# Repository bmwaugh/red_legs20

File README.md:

# red_legs20
Git Repository for Red Legs 20 MQP

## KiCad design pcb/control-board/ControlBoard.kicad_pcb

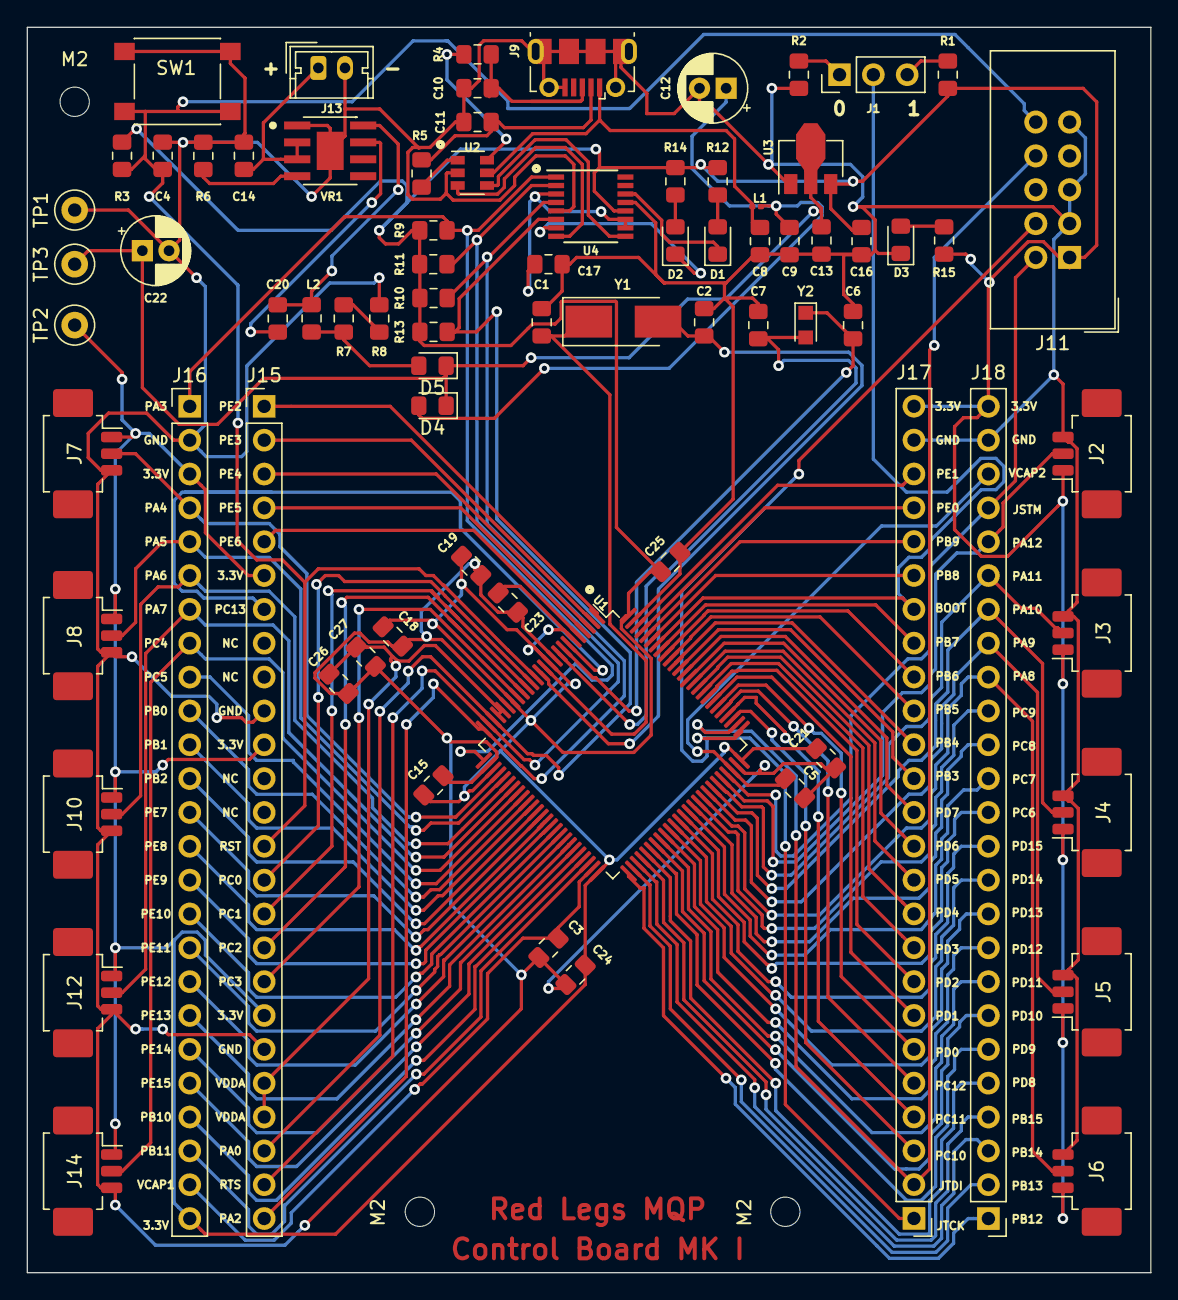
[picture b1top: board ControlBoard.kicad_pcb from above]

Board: 2 copper layers, 84.3 x 93.5 mm, 81 parts (0 on the bottom side), 112 nets.

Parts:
C1, C2: 22p; C_0805_2012Metric_Pad1.15x1.40mm_HandSolder
C3, C5, C14: 2.2uF; C_0805_2012Metric_Pad1.15x1.40mm_HandSolder
C4: 0.1uF; C_0805_2012Metric_Pad1.15x1.40mm_HandSolder
C6, C7: 10p; C_0805_2012Metric_Pad1.15x1.40mm_HandSolder
C8: 10nF; C_0805_2012Metric_Pad1.15x1.40mm_HandSolder
C9, C15, C17, C18, C19, C21, C23, C24, C25, C26: 100nF; C_0805_2012Metric_Pad1.15x1.40mm_HandSolder
C10, C11: 47pF; C_0805_2012Metric_Pad1.15x1.40mm_HandSolder
C12: 4.7uF; CP_Radial_D5.0mm_P2.00mm
C13, C16, C27: 1uF; C_0805_2012Metric_Pad1.15x1.40mm_HandSolder
C20: 2.2nF; C_0805_2012Metric_Pad1.15x1.40mm_HandSolder
C22: 47uF; CP_Radial_D5.0mm_P2.00mm
D1, D2, D3: LED; LED_0805_2012Metric_Pad1.15x1.40mm_HandSolder
D4, D5: SD0805; D_0805_2012Metric_Pad1.15x1.40mm_HandSolder
J1: BOOT0; PinHeader_1x03_P2.54mm_Vertical
J2: Motor1; Molex_PicoBlade_53261-0371_1x03-1MP_P1.25mm_Horizontal
J3: Motor2; Molex_PicoBlade_53261-0371_1x03-1MP_P1.25mm_Horizontal
J4: Motor3; Molex_PicoBlade_53261-0371_1x03-1MP_P1.25mm_Horizontal
J5: Motor4; Molex_PicoBlade_53261-0371_1x03-1MP_P1.25mm_Horizontal
J6: Motor5; Molex_PicoBlade_53261-0371_1x03-1MP_P1.25mm_Horizontal
J7: Motor6; Molex_PicoBlade_53261-0371_1x03-1MP_P1.25mm_Horizontal
J8: Motor7; Molex_PicoBlade_53261-0371_1x03-1MP_P1.25mm_Horizontal
J9: USB_B_Micro; USB_Micro-B_Molex-105017-0001
J10: Motor8; Molex_PicoBlade_53261-0371_1x03-1MP_P1.25mm_Horizontal
J11: JTAG-SWD; IDC-Header_2x05_P2.54mm_Vertical
J12: Motor9; Molex_PicoBlade_53261-0371_1x03-1MP_P1.25mm_Horizontal
J13: PWR; Molex_Micro-Latch_53253-0270_1x02_P2.00mm_Vertical
J14: Motor10; Molex_PicoBlade_53261-0371_1x03-1MP_P1.25mm_Horizontal
J15: HEADER_L; PinHeader_1x25_P2.54mm_Vertical
J16: HEADER_D; PinHeader_1x25_P2.54mm_Vertical
J17: HEADER_U; PinHeader_1x25_P2.54mm_Vertical
J18: HEADER_R; PinHeader_1x25_P2.54mm_Vertical
L1: BK0603HS330-T; L_0201_0603Metric
L2: 68uH; L_0805_2012Metric_Pad1.15x1.40mm_HandSolder
M2, M2#2, M2#3: MountingHole_2.2mm_M2
R1, R2, R3, R9, R10, R11, R13: 10K; R_0805_2012Metric_Pad1.15x1.40mm_HandSolder
R4, R5: 27R; R_0805_2012Metric_Pad1.15x1.40mm_HandSolder
R6: 2.5k; R_0805_2012Metric_Pad1.15x1.40mm_HandSolder
R7: 100k; R_0805_2012Metric_Pad1.15x1.40mm_HandSolder
R8: 31.6k; R_0805_2012Metric_Pad1.15x1.40mm_HandSolder
R12, R14, R15: 220; R_0805_2012Metric_Pad1.15x1.40mm_HandSolder
SW1: RST_BTN; SW_Push_1P1T_NO_6x6mm_H9.5mm
TP1, TP2, TP3: TestPoint; TestPoint_Loop_D2.50mm_Drill1.0mm
U1: STM32F427VGTx; LQFP-100_14x14mm_P0.5mm
U2: USBLC6-2SC6; SOT-23-6
U3: MCP1700-3302E_SOT89; SOT-89-3
U4: FT230XS; SSOP-16_3.9x4.9mm_P0.635mm
VR1: LM5164DDAR; SOIC127P600X170-9N
Y1: 8MHz; Crystal_SMD_5032-2Pin_5.0x3.2mm_HandSoldering
Y2: 32.768kHz; Crystal_SMD_2012-2Pin_2.0x1.2mm_HandSoldering

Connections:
3.3V: C15.1, C16.1, C18.1, C19.1, C21.1, C23.1, C24.1, C25.1, J2.1, J3.1, J4.1, J5.1, J6.1, J7.1, J8.1, J10.1, J11.1, J12.1, J14.1, J15.6, J15.11, J15.19, J16.3, J16.25, J17.25, J18.25, R1.1, R3.1, R9.1, R10.1, R11.1, R12.1, R13.1, R14.1, R15.1, TP2.1, U1.6, U1.11, U1.19, U1.28, U1.50, U1.75, U1.100, U3.3, U4.12
5V: C13.1, C22.1, D4.1, D5.1, TP3.1, U3.2
/RXLED: D2.1, U4.7
/TXLED: D1.1, U4.14
BOOT0: J1.2, J17.19, U1.94
GND: C1.1, C2.2, C3.2, C4.2, C5.2, C6.2, C7.1, C8.2, C9.2, C10.2, C11.2, C12.2, C13.2, C14.2, C15.2, C16.2, C17.2, C18.2, C19.2, C21.2, C22.2, C23.2, C24.2, C25.2, C26.2, C27.2, D3.1, J2.3, J3.3, J4.3, J5.3, J6.3, J7.3, J8.3, J9.5, J9.6, J10.3, J11.3, J11.5, J11.9, J12.3, J13.2, J14.3, J15.10, J15.20, J16.2, J17.24, J18.24, R2.2, R6.2, R8.2, SW1.1, TP1.1, U1.10, U1.20, U1.27, U1.74, U1.99, U2.2, U3.1, U4.5, U4.13, VR1.1, VR1.9
JSTM: J11.2, J18.22, U1.72
JTCK: J11.4, J17.1, U1.76
JTDI: J11.8, J17.2, U1.77
unnamed: C1.2, U1.12, Y1.1
unnamed: C2.1, U1.13, Y1.2
unnamed: C6.1, U1.8, Y2.1
unnamed: C7.2, U1.9, Y2.2
unnamed: C10.1, J9.3, R4.2
unnamed: C11.1, J9.2, R5.2
unnamed: C9.1, C12.1, D4.2, L1.2
unnamed: C20.1, L2.1, VR1.8
unnamed: C20.2, VR1.7
unnamed: D1.2, R12.2
unnamed: D2.2, R14.2
unnamed: D3.2, R15.2
unnamed: D5.2, L2.2, R7.1
unnamed: J1.1, R2.1
unnamed: J1.3, R1.2
unnamed: R4.1, U2.6
unnamed: R5.1, U2.1
unnamed: R6.1, VR1.4
unnamed: R7.2, R8.1
unnamed: U2.3, U4.8
unnamed: U2.4, U4.9
PA0-CTS: J15.23, R13.2, U1.23, U4.6
PA1-RTS: J15.24, R11.2, U1.24, U4.2
PA2-TX: J15.25, R10.2, U1.25, U4.4
PA3-RX: J16.1, R9.2, U1.26, U4.1
PA4: J7.2, J16.4, U1.29
PA5: J8.2, J16.5, U1.30
PA6: J10.2, J16.6, U1.31
PA7: J12.2, J16.7, U1.32
PA8: J6.2, J18.17, U1.67
PA9: J5.2, J18.18, U1.68
PA10: J4.2, J18.19, U1.69
PA11: J3.2, J18.20, U1.70
PA12: J2.2, J18.21, U1.71
PB0: J16.10, U1.35
PB1: J16.11, U1.36
PB2: J16.12, U1.37
PB3: J17.14, U1.89
PB4: J17.15, U1.90
PB5: J17.16, U1.91
PB6: J17.17, U1.92
PB7: J17.18, U1.93
PB8: J17.20, U1.95
PB9: J17.21, U1.96
PB10: J16.22, U1.47
PB11: J16.23, U1.48
PB12: J18.1, U1.51
PB13: J18.2, U1.52
PB14: J18.3, U1.53
PB15: J18.4, U1.54
PC0: J15.15, U1.15
PC1: J15.16, U1.16
PC2: J15.17, U1.17
PC3: J15.18, U1.18
PC4: J14.2, J16.8, U1.33
PC5: J16.9, U1.34
PC6: J18.13, U1.63
PC7: J18.14, U1.64
PC8: J18.15, U1.65
PC9: J18.16, U1.66
PC10: J17.3, U1.78
PC11: J17.4, U1.79
PC12: J17.5, U1.80
PC13: J15.7, U1.7
PD0: J17.6, U1.81
PD1: J17.7, U1.82
PD2: J17.8, U1.83
PD3: J17.9, U1.84
PD4: J17.10, U1.85
PD5: J17.11, U1.86
PD6: J17.12, U1.87
PD7: J17.13, U1.88
PD8: J18.5, U1.55
PD9: J18.6, U1.56
PD10: J18.7, U1.57
PD11: J18.8, U1.58
PD12: J18.9, U1.59
PD13: J18.10, U1.60
PD14: J18.11, U1.61
PD15: J18.12, U1.62
PE0: J17.22, U1.97
PE1: J17.23, U1.98
PE2: J15.1, U1.1
PE3: J15.2, U1.2
PE4: J15.3, U1.3
PE5: J15.4, U1.4
PE6: J15.5, U1.5
PE7: J16.13, U1.38
PE8: J16.14, U1.39
PE9: J16.15, U1.40
PE10: J16.16, U1.41
PE11: J16.17, U1.42
PE12: J16.18, U1.43
PE13: J16.19, U1.44
PE14: J16.20, U1.45
PE15: J16.21, U1.46
RESET: C17.1, U4.3, U4.10, U4.11
VBUS: C8.1, J9.1, L1.1, U2.5
VCAP1: C3.1, J16.24, U1.49
VCAP2: C5.1, J18.23, U1.73
VCC: C14.1, J13.1, VR1.2, VR1.3
VDDA: C26.1, C27.1, J15.21, J15.22, U1.21, U1.22
nJRST: C4.1, J11.10, J15.14, R3.2, SW1.2, U1.14

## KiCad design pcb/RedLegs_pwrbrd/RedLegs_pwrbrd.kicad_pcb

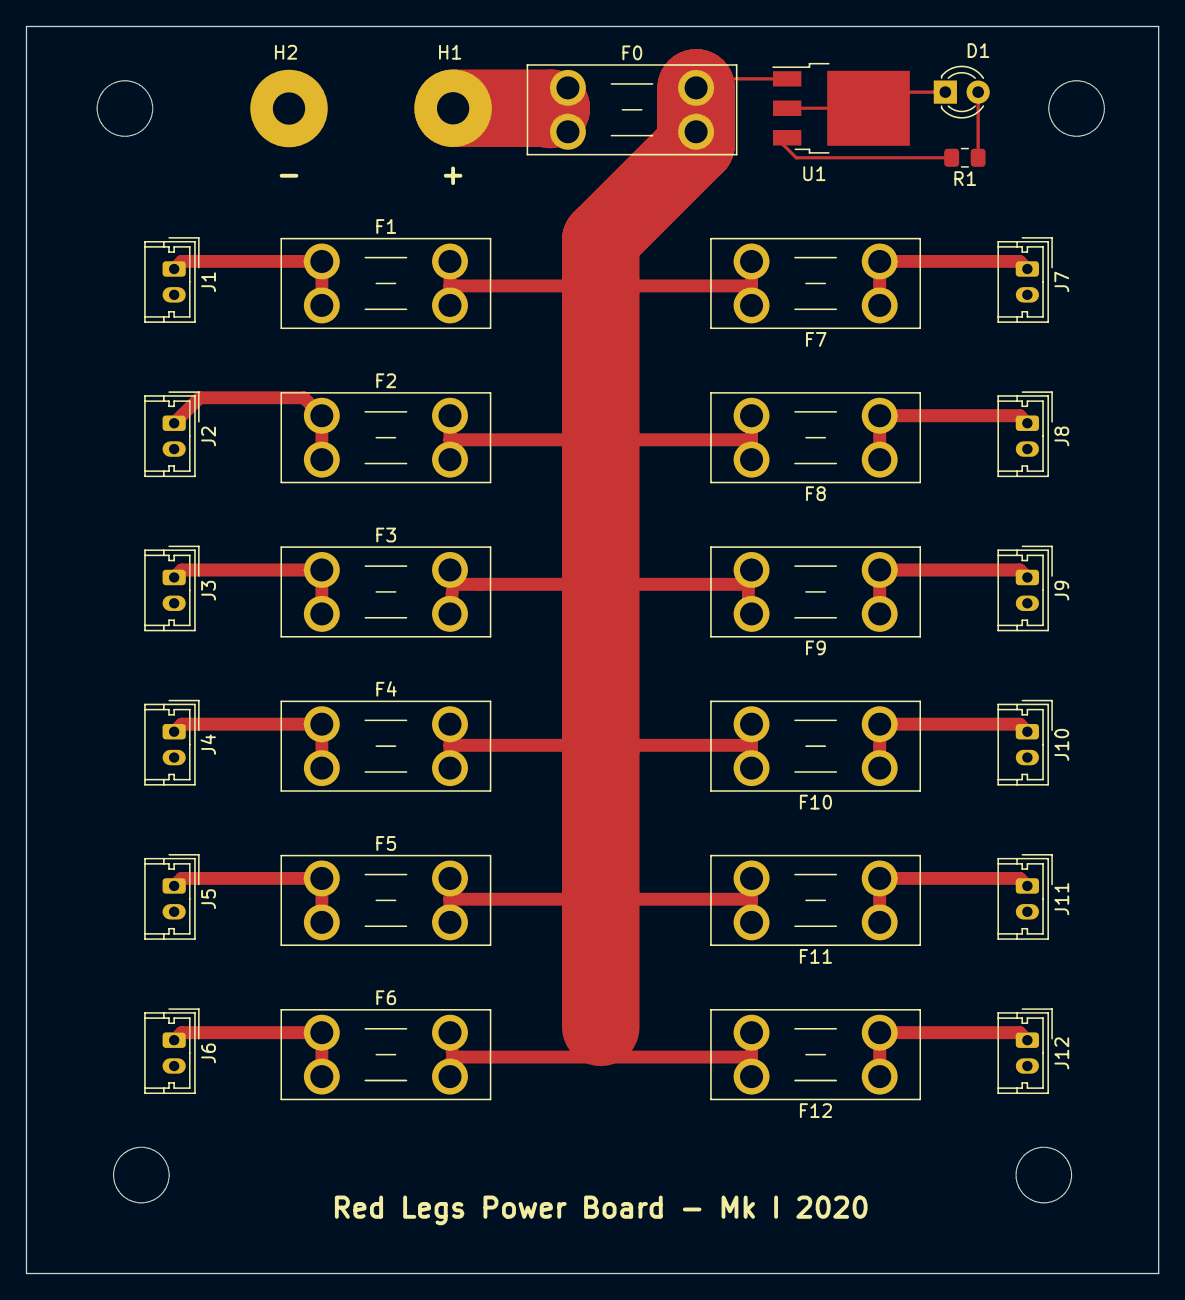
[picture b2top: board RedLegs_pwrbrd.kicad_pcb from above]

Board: 2 copper layers, 87.6 x 96.5 mm, 31 parts (0 on the bottom side), 17 nets.

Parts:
D1: LED; LED_D3.0mm
F0, F1, F2, F3, F4, F5, F6, F7, F8, F9, F10, F11, F12: Fuse; Fuseholder_Blade_Mini_Keystone_3568
H1: BATT_VCC; SolderWirePad_1x01_Drill2.5mm
H2: BATT_GND; SolderWirePad_1x01_Drill2.5mm
J1, J2, J3, J4, J5, J6, J7, J8, J9, J10, J11, J12: Conn_01x02; Molex_Micro-Latch_53253-0270_1x02_P2.00mm_Vertical
Mnt_Hole: M4; MountingHole_4.3mm_M4
R1: 330; R_0805_2012Metric_Pad1.15x1.40mm_HandSolder
U1: L7805; TO-252-3_TabPin2

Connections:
+BATT: F0.1, H1.1
GND: D1.1, H2.1, J1.2, J2.2, J3.2, J4.2, J5.2, J6.2, J7.2, J8.2, J9.2, J10.2, J11.2, J12.2, U1.2
unnamed: D1.2, R1.1
unnamed: F1.1, J1.1
unnamed: F2.1, J2.1
unnamed: F3.1, J3.1
unnamed: F4.1, J4.1
unnamed: F5.1, J5.1
unnamed: F6.1, J6.1
unnamed: F7.1, J7.1
unnamed: F8.1, J8.1
unnamed: F9.1, J9.1
unnamed: F10.1, J10.1
unnamed: F11.1, J11.1
unnamed: F12.1, J12.1
unnamed: R1.2, U1.3
VCC: F0.2, F1.2, F2.2, F3.2, F4.2, F5.2, F6.2, F7.2, F8.2, F9.2, F10.2, F11.2, F12.2, U1.1

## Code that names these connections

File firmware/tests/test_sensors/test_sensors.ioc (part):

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Mcu.Name=STM32F103C(8-B)Tx
Mcu.Package=LQFP48
Mcu.UserName=STM32F103C8Tx
PA5.Signal=GPIO_Analog
PA8.Signal=GPIO_Output
PA9.Signal=GPIO_Output
PB12.Signal=GPIO_Output
PB13.Signal=GPIO_Output
PB14.Signal=GPIO_Output
PB15.Signal=GPIO_Output
PB5.GPIOParameters=GPIO_PuPd
PB5.GPIO_PuPd=GPIO_PULLUP
PB5.Signal=GPIO_Input
PB6.GPIOParameters=GPIO_PuPd
PB6.GPIO_PuPd=GPIO_PULLUP
PB6.Signal=GPIO_Input
PC13-TAMPER-RTC.Signal=GPIO_Output
board=custom

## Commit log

2019-11-13 hello world
2020-02-03 Added KICAD files for mainboard
    still a work in progress
2020-02-09 Added breakout board for 3pin molex
2020-02-09 updated to the main board
2020-02-09 added v2
2020-02-09 Changed naming convention
2020-02-12 finish power circuitry
2020-02-12 finished power circuitry
2020-02-12 ther commit wasnt complete
2020-02-13 Generated gerber files for breakout board
2020-02-13 Control board power supply
2020-02-16 Added power distribution board. Needs to be reviewed. Traces need to be added.
2020-02-17 Minor control board fixes (schematic)
2020-03-01 Fixed power schematic, working on pcb
2020-03-02 Finish placement, added master fuse
2020-03-02 serialread from computer
2020-03-02 added commits to serailread
2020-03-02 Finished routing wires, adding silkscreen
2020-03-02 More routing..
2020-03-04 Finish power board
2020-03-05 Adding power + jtag to control board
2020-03-05 Working on serial integration with the stm32
2020-03-23 Added Gerber files
2020-04-01 Finishing control schematic
2020-04-05 Routing control board
2020-04-06 AHRS still has a few bugs
2020-04-06 Finish control board pcb
2020-04-08 Added solder paste layer to plot
2020-04-26 Working on AHRS messsages. Need Max232.
2020-04-26 Added powerboard image
